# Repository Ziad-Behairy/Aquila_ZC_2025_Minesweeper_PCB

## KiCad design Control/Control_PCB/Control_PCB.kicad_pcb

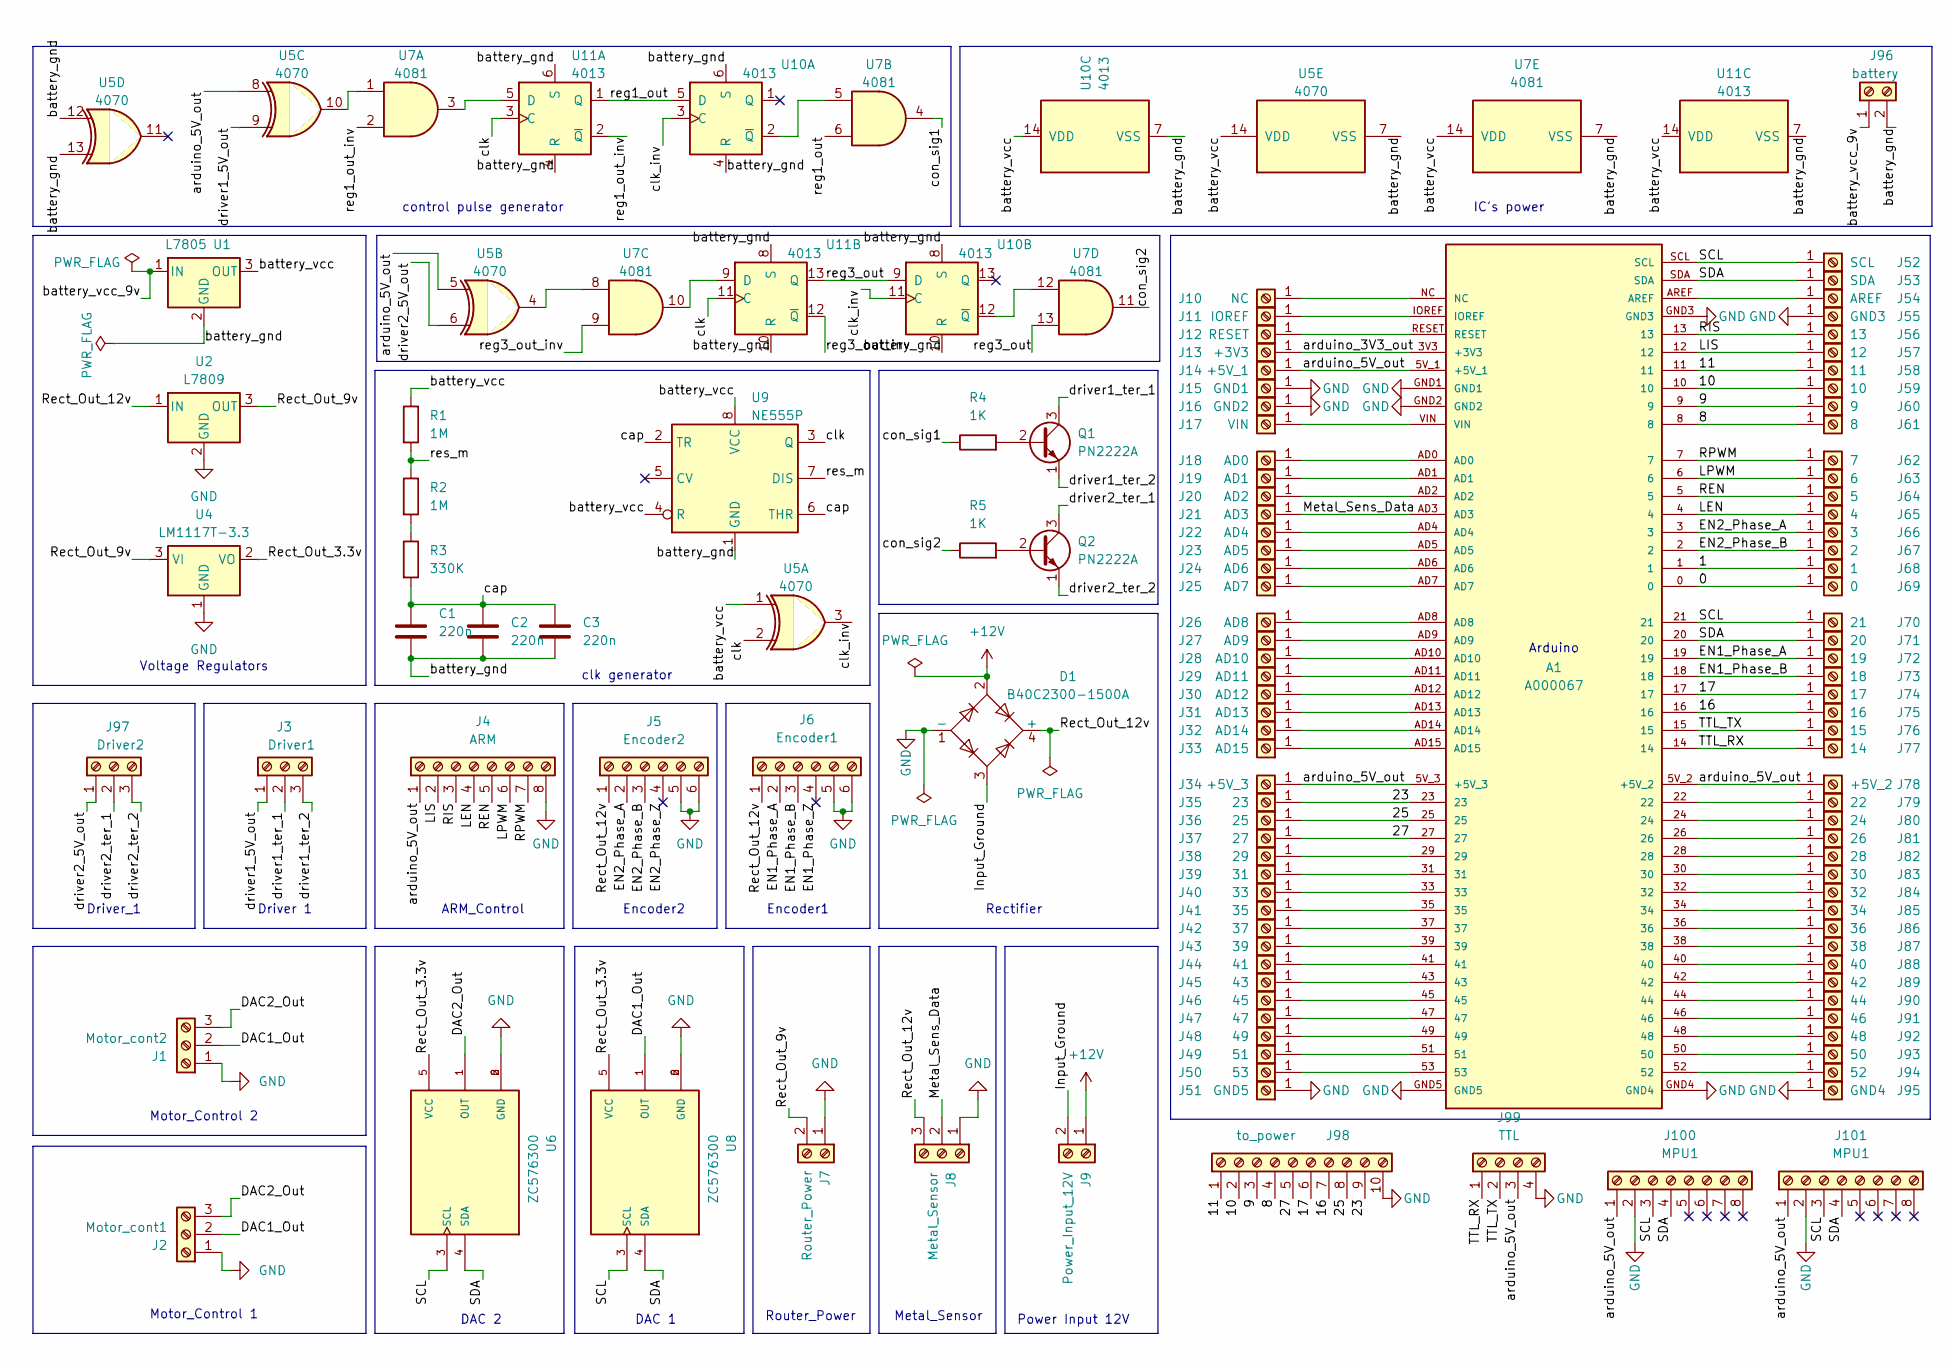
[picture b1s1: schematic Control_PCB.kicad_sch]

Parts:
A1: A000067; Arduino_Mega
C1, C2, C3: 220n; C_Disc_D7.5mm_W5.0mm_P7.50mm
D1: B40C2300-1500A; Diode_Bridge_19.0x3.5x10.0mm_P5.0mm
J1: Motor_cont2; JST_XH_B3B-XH-A_1x03_P2.50mm_Vertical
J2: Motor_cont1; JST_XH_B3B-XH-A_1x03_P2.50mm_Vertical
J3: Driver1; JST_XH_B3B-XH-A_1x03_P2.50mm_Vertical
J4: ARM; JST_XH_B8B-XH-A_1x08_P2.50mm_Vertical
J5: Encoder2; JST_XH_B6B-XH-A_1x06_P2.50mm_Vertical
J6: Encoder1; JST_XH_B6B-XH-A_1x06_P2.50mm_Vertical
J7: Router_Power; TerminalBlock_bornier-2_P5.08mm
J8: Metal_Sensor; TerminalBlock_bornier-3_P5.08mm
J9: Power_Input_12V; TerminalBlock_bornier-2_P5.08mm
J10: NC; Pin_Hole_0.9
J11: IOREF; Pin_Hole_0.9
J12: RESET; Pin_Hole_0.9
J13: +3V3; Pin_Hole_0.9
J14: +5V_1; Pin_Hole_0.9
J15: GND1; Pin_Hole_0.9
J16: GND2; Pin_Hole_0.9
J17: VIN; Pin_Hole_0.9
J18: AD0; Pin_Hole_0.9
J19: AD1; Pin_Hole_0.9
J20: AD2; Pin_Hole_0.9
J21: AD3; Pin_Hole_0.9
J22: AD4; Pin_Hole_0.9
J23: AD5; Pin_Hole_0.9
J24: AD6; Pin_Hole_0.9
J25: AD7; Pin_Hole_0.9
J26: AD8; Pin_Hole_0.9
J27: AD9; Pin_Hole_0.9
J28: AD10; Pin_Hole_0.9
J29: AD11; Pin_Hole_0.9
J30: AD12; Pin_Hole_0.9
J31: AD13; Pin_Hole_0.9
J32: AD14; Pin_Hole_0.9
J33: AD15; Pin_Hole_0.9
J34: +5V_3; Pin_Hole_0.9
J35: 23; Pin_Hole_0.9
J36: 25; Pin_Hole_0.9
J37: 27; Pin_Hole_0.9
J38: 29; Pin_Hole_0.9
J39: 31; Pin_Hole_0.9
J40: 33; Pin_Hole_0.9
J41: 35; Pin_Hole_0.9
J42: 37; Pin_Hole_0.9
J43: 39; Pin_Hole_0.9
J44: 41; Pin_Hole_0.9
J45: 43; Pin_Hole_0.9
J46: 45; Pin_Hole_0.9
J47: 47; Pin_Hole_0.9
J48: 49; Pin_Hole_0.9
J49: 51; Pin_Hole_0.9
J50: 53; Pin_Hole_0.9
J51: GND5; Pin_Hole_0.9
J52: SCL; Pin_Hole_0.9
J53: SDA; Pin_Hole_0.9
J54: AREF; Pin_Hole_0.9
J55: GND3; Pin_Hole_0.9
J56: 13; Pin_Hole_0.9
J57: 12; Pin_Hole_0.9
J58: 11; Pin_Hole_0.9
J59: 10; Pin_Hole_0.9
J60: 9; Pin_Hole_0.9
J61: 8; Pin_Hole_0.9
J62: 7; Pin_Hole_0.9
J63: 6; Pin_Hole_0.9
J64: 5; Pin_Hole_0.9
J65: 4; Pin_Hole_0.9
J66: 3; Pin_Hole_0.9
J67: 2; Pin_Hole_0.9
J68: 1; Pin_Hole_0.9
J69: 0; Pin_Hole_0.9
J70: 21; Pin_Hole_0.9
J71: 20; Pin_Hole_0.9
J72: 19; Pin_Hole_0.9
J73: 18; Pin_Hole_0.9
J74: 17; Pin_Hole_0.9
J75: 16; Pin_Hole_0.9
J76: 15; Pin_Hole_0.9
J77: 14; Pin_Hole_0.9
J78: +5V_2; Pin_Hole_0.9
J79: 22; Pin_Hole_0.9
J80: 24; Pin_Hole_0.9
J81: 26; Pin_Hole_0.9
J82: 28; Pin_Hole_0.9
J83: 30; Pin_Hole_0.9
J84: 32; Pin_Hole_0.9
J85: 34; Pin_Hole_0.9
J86: 36; Pin_Hole_0.9
J87: 38; Pin_Hole_0.9
J88: 40; Pin_Hole_0.9
J89: 42; Pin_Hole_0.9
J90: 44; Pin_Hole_0.9
J91: 46; Pin_Hole_0.9
J92: 48; Pin_Hole_0.9
J93: 50; Pin_Hole_0.9
J94: 52; Pin_Hole_0.9
J95: GND4; Pin_Hole_0.9
J96: battery; JST_XH_B2B-XH-A_1x02_P2.50mm_Vertical
J97: Driver2; JST_XH_B3B-XH-A_1x03_P2.50mm_Vertical
J98: to_power; JST_XH_B10B-XH-A_1x10_P2.50mm_Vertical
J99: TTL; JST_XH_B4B-XH-A_1x04_P2.50mm_Vertical
J100, J101: MPU1; module_mpu6050
Q1, Q2: PN2222A; TO-92L_Inline_Wide
R1, R2: 1M; R_Axial_DIN0204_L3.6mm_D1.6mm_P7.62mm_Horizontal
R3: 330K; R_Axial_DIN0204_L3.6mm_D1.6mm_P7.62mm_Horizontal
R4, R5: 1K; R_Axial_DIN0204_L3.6mm_D1.6mm_P7.62mm_Horizontal
U1: L7805; TO-220-3_Vertical
U2: L7809; TO-220-3_Vertical
U4: LM1117T-3.3; TO-220-3_Vertical
U5: 4070; DIP-14_W7.62mm_LongPads
U6, U8: ZC576300; MODULE_ZC576300; PARTREV v14
U7: 4081; DIP-14_W7.62mm_LongPads
U9: NE555P; DIP-8_W7.62mm
U10, U11: 4013; DIP-14_W7.62mm_LongPads

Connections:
+12V: D1.2, J9.1
/0: A1.0, J69.1
/1: A1.1, J68.1
/8: A1.8, J61.1, J98.4
/9: A1.9, J60.1, J98.3
/10: A1.10, J59.1, J98.2
/11: A1.11, J58.1, J98.1
/16: A1.16, J75.1, J98.7
/17: A1.17, J74.1, J98.6
/23: A1.23, J35.1, J98.9
/25: A1.25, J36.1, J98.8
/27: A1.27, J37.1, J98.5
/DAC1_Out: J1.2, J2.2, U8.1 (OUT)
/DAC2_Out: J1.3, J2.3, U6.1 (OUT)
/EN1_Phase_A: A1.19, J6.2, J72.1
/EN1_Phase_B: A1.18, J6.3, J73.1
/EN1_Phase_Z: J6.4
/EN2_Phase_A: A1.3, J5.2, J66.1
/EN2_Phase_B: A1.2, J5.3, J67.1
/EN2_Phase_Z: J5.4
/Input_Ground: D1.3, J9.2
/LEN: A1.4, J4.4, J65.1
/LIS: A1.12, J4.2, J57.1
/LPWM: A1.6, J4.6, J63.1
/Metal_Sens_Data: A1.AD3, J8.2, J21.1
/REN: A1.5, J4.5, J64.1
/RIS: A1.13, J4.3, J56.1
/RPWM: A1.7, J4.7, J62.1
/Rect_Out_3.3v: U4.2 (VO), U6.5 (VCC), U8.5 (VCC)
/Rect_Out_9v: J7.2, U2.3 (OUT), U4.3 (VI)
/Rect_Out_12v: D1.4 (+), J5.1, J6.1, J8.3, U2.1 (IN)
/SCL: A1.21, A1.SCL, J52.1, J70.1, J100.3, J101.3, U6.3 (SCL), U8.3 (SCL)
/SDA: A1.20, A1.SDA, J53.1, J71.1, J100.4, J101.4, U6.4 (SDA), U8.4 (SDA)
/TTL_RX: A1.14, J77.1, J99.1; also elsewhere on the board
/TTL_TX: A1.15, J76.1, J99.2; also elsewhere on the board
/arduino_3V3_out: A1.3V3 (+3V3), J13.1
/arduino_5V_out: A1.5V_1 (+5V_1), A1.5V_2 (+5V_2), A1.5V_3 (+5V_3), J4.1, J14.1, J34.1, J78.1, J99.3, J100.1, J101.1, U5.5, U5.8; also elsewhere on the board
/battery_gnd: C1.2, C2.2, C3.2, J96.2, U1.2 (GND), U5.7 (VSS), U5.12, U5.13, U7.7 (VSS), U9.1 (GND), U10.4 (R), U10.6 (S), U10.7 (VSS), U10.8 (S), U10.10 (R), U11.4 (R), U11.6 (S), U11.7 (VSS), U11.8 (S), U11.10 (R)
/battery_vcc: R1.1, U1.3 (OUT), U5.1, U5.14 (VDD), U7.14 (VDD), U9.4 (R), U9.8 (VCC), U10.14 (VDD), U11.14 (VDD)
/battery_vcc_9v: J96.1, U1.1 (IN)
/cap: C1.1, C2.1, C3.1, R3.2, U9.2 (TR), U9.6 (THR)
/clk: U5.2, U9.3 (Q), U11.3 (C), U11.11 (C)
/clk_inv: U5.3, U10.3 (C), U10.11 (C)
/con_sig1: R4.1, U7.4
/con_sig2: R5.1, U7.11
/driver1_5V_out: J3.1, U5.9
/driver1_ter_1: J3.2, Q1.3 (C)
/driver1_ter_2: J3.3, Q1.1 (E)
/driver2_5V_out: J97.1, U5.6
/driver2_ter_1: J97.2, Q2.3 (C)
/driver2_ter_2: J97.3, Q2.1 (E)
/reg1_out: U7.6, U10.5 (D), U11.1 (Q)
/reg1_out_inv: U7.2, U11.2 (~Q)
/reg3_out: U7.13, U10.9 (D), U11.13 (Q)
/reg3_out_inv: U7.9, U11.12 (~Q)
/res_m: R1.2, R2.1, U9.7 (DIS)
GND: A1.GND1, A1.GND2, A1.GND3, A1.GND4, A1.GND5, D1.1 (-), J1.1, J2.1, J4.8, J5.5, J5.6, J6.5, J6.6, J7.1, J8.1, J15.1, J16.1, J51.1, J55.1, J95.1, J98.10, J99.4, J100.2, J101.2, U2.2 (GND), U4.1 (GND), U6.2 (GND), U6.6 (GND), U8.2 (GND), U8.6 (GND); also elsewhere on the board
unnamed: A1.NC, J10.1
unnamed: A1.IOREF, J11.1
unnamed: A1.RESET, J12.1
unnamed: A1.VIN, J17.1
unnamed: A1.AD0, J18.1
unnamed: A1.AD1, J19.1
unnamed: A1.AD2, J20.1
unnamed: A1.AD4, J22.1
unnamed: A1.AD5, J23.1
unnamed: A1.AD6, J24.1
unnamed: A1.AD7, J25.1
unnamed: A1.AD8, J26.1
unnamed: A1.AD9, J27.1
unnamed: A1.AD10, J28.1
unnamed: A1.AD11, J29.1
unnamed: A1.AD12, J30.1
unnamed: A1.AD13, J31.1
unnamed: A1.AD14, J32.1
unnamed: A1.AD15, J33.1
unnamed: A1.29, J38.1
unnamed: A1.31, J39.1
unnamed: A1.33, J40.1
unnamed: A1.35, J41.1
unnamed: A1.37, J42.1
unnamed: A1.39, J43.1
unnamed: A1.41, J44.1
unnamed: A1.43, J45.1
unnamed: A1.45, J46.1
unnamed: A1.47, J47.1
unnamed: A1.49, J48.1
unnamed: A1.51, J49.1
unnamed: A1.53, J50.1
unnamed: A1.AREF, J54.1
unnamed: A1.22, J79.1
unnamed: A1.24, J80.1
unnamed: A1.26, J81.1
unnamed: A1.28, J82.1
unnamed: A1.30, J83.1
unnamed: A1.32, J84.1
unnamed: A1.34, J85.1
unnamed: A1.36, J86.1
unnamed: A1.38, J87.1
unnamed: A1.40, J88.1
unnamed: A1.42, J89.1
unnamed: A1.44, J90.1
unnamed: A1.46, J91.1
unnamed: A1.48, J92.1
unnamed: A1.50, J93.1
unnamed: A1.52, J94.1
unnamed: Q1.2 (B), R4.2
unnamed: Q2.2 (B), R5.2
unnamed: R2.2, R3.1
unnamed: U5.4, U7.8
unnamed: U5.10, U7.1
unnamed: U7.5, U10.2 (~Q)
unnamed: U7.12, U10.12 (~Q)
unnamed: U7.3, U11.5 (D)
unnamed: U7.10, U11.9 (D)

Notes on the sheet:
Driver_1
clk generator
Voltage Regulators
Power Input 12V
Router_Power
ARM_Control
DAC 1
IC's power
Rectifier
Encoder2
Motor_Control 1
Arduino
Encoder1
Metal_Sensor
Motor_Control 2
DAC 2
control pulse generator
Driver 1

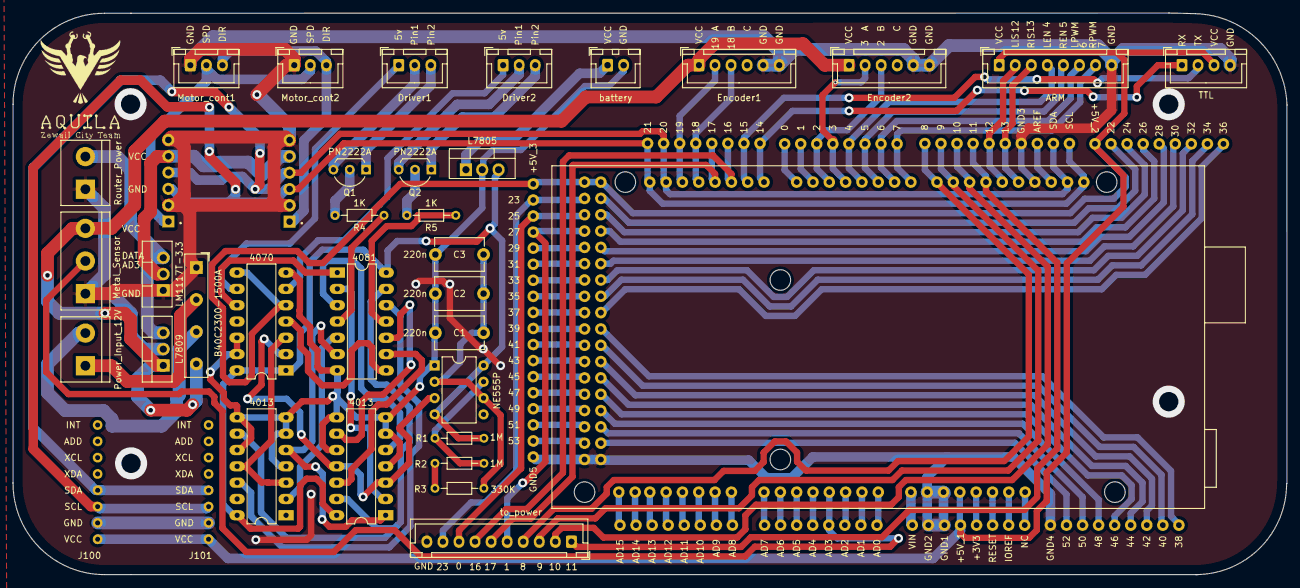
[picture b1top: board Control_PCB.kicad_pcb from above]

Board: 2 copper layers, 198.3 x 87.4 mm, 123 parts (0 on the bottom side), 113 nets.

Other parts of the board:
TTL: TTL; JST_XH_B4B-XH-A_1x04_P2.50mm_Vertical

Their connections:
/TTL_RX: TTL.1; also elsewhere on the board
/TTL_TX: TTL.2; also elsewhere on the board
/arduino_5V_out: TTL.3; also elsewhere on the board
GND: TTL.4; also elsewhere on the board
